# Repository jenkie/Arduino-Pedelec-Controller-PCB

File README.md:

# Arduino-Pedelec-Controller-PCB
PCB files for the Arduino Pedelec Controller

More info see http://www.pedelecforum.de/wiki/doku.php?id=elektrotechnik:forumscontroller

Shield: [![CC BY-NC 4.0][cc-by-nc-shield]][cc-by-nc]

This work is licensed under a
[Creative Commons Attribution-NonCommercial 4.0 International License][cc-by-nc].

[![CC BY-NC 4.0][cc-by-nc-image]][cc-by-nc]

[cc-by-nc]: https://creativecommons.org/licenses/by-nc/4.0/
[cc-by-nc-image]: https://licensebuttons.net/l/by-nc/4.0/88x31.png
[cc-by-nc-shield]: https://img.shields.io/badge/License-CC%20BY--NC%204.0-lightgrey.svg

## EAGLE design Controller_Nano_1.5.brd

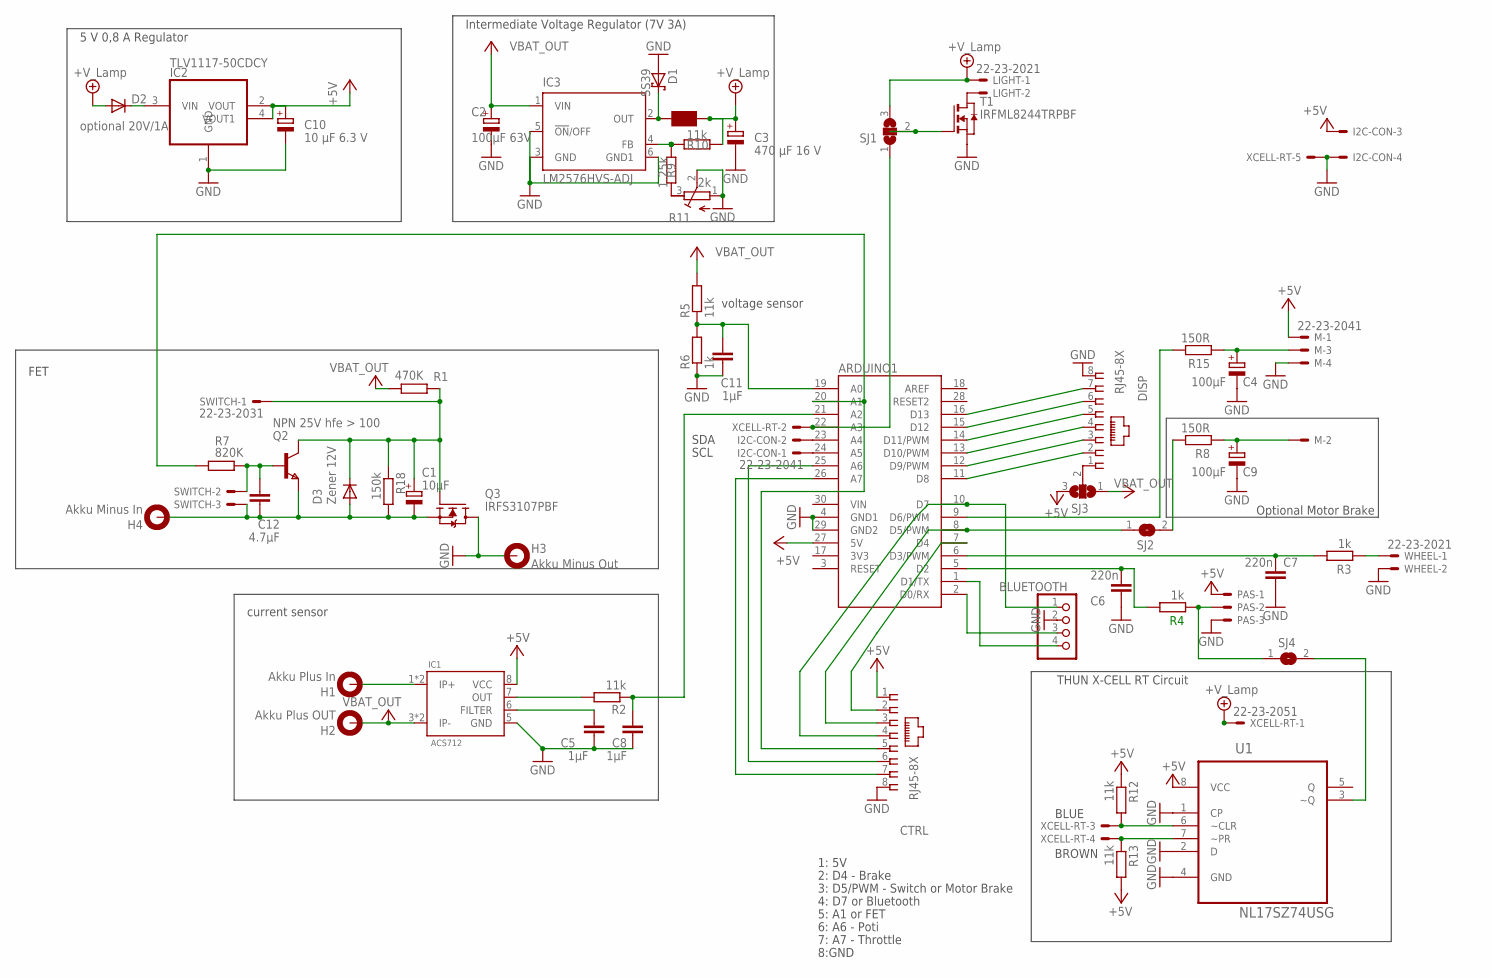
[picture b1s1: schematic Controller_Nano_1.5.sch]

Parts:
ARDUINO1: ARDUINO_NANO_CHECKED
BLUETOOTH: PINHD-1X4; 1X04
C1: 10µF; E2-5
C2: 100µF 63V; E3,5-8
C3: 470 µF 16 V; E3,5-8
C4, C9: 100µF; E2-5
C5, C8, C11: 1µF; C0805
C6, C7: 220n; C0805
C10: 10 µF 6.3 V; E2-5
C12: 4.7µF; C0805
CTRL: RJ45-8X; RJ45-NO-SHIELD
D1: SS39; SMC
D2: optional 20V/1A; DO-214AC
D3: Zener 12V; SOD323-W
DISP: RJ45-8X; RJ45-NO-SHIELD
H1: Akku Plus In; 2,8-PAD
H2: Akku Plus OUT; 2,8-PAD
H3: Akku Minus Out; 2,8-PAD
H4: Akku Minus In; 2,8-PAD
I2C-CON: 22-23-2041
IC1: ACS712; MARTIN-SMD-IC_SO-8
IC2: TLV1117-50CDCY; SOT223
IC3: LM2576HVS-ADJ; TO263-5
LIGHT: 22-23-2021; MPN 22-23-2021
M: 22-23-2041; MPN 22-23-2041
PAS: 22-23-2031
Q2: NPN 25V hfe > 100; SOT-23
Q3: IRFS3107PBF; TRANSISTOR-FET_TO263
R1: 470K; R1206
R2, R5, R10, R12, R13: 11k; R1206
R3, R4, R6: 1k; R1206
R7: 820K; R1206
R8, R15: 150R; R1206
R9: 1.25k; R1206
R11: 2k; RTRIM3103
R18: 150k; R1206
SJ1, SJ3: SJ2WW; SJ_2W
SJ2, SJ4: SJ
SWITCH: 22-23-2031; MPN 22-23-2031
T1: IRFML8244TRPBF; SOT-23
U1: NL17SZ74USG; SOP50P310X90-8N
U$1: PIST-151
WHEEL: 22-23-2021
XCELL-RT: 22-23-2051

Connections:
3V3: ARDUINO1.17 (3V3)
+5V: ARDUINO1.27 (5V), C10.+, CTRL.1, I2C-CON.3, IC1.8 (VCC), IC2.2 (VOUT), IC2.4 (VOUT1), M.1, PAS.1, R12.1, R13.2, SJ3.3, U1.8 (VCC)
+5V/2: C3.+, D2.A, LIGHT.1, R10.1, SJ1.3, U$1.P$2, XCELL-RT.1
GND: ARDUINO1.4 (GND1), ARDUINO1.29 (GND2), BLUETOOTH.2, C2.-, C3.-, C4.-, C5.2, C6.2, C7.2, C8.2, C9.-, C10.-, C11.2, CTRL.8, D1.A, DISP.8, H3.B2,8, I2C-CON.4, IC1.5 (GND), IC2.1 (GND), IC3.3 (GND), IC3.5 (!ON!/OFF), IC3.6 (GND1), M.4, PAS.3, Q3.2D (D), R6.1, R11.1 (E), R11.2 (S), T1.2 (S), U1.1 (CP), U1.2 (D), U1.4 (GND), WHEEL.2, XCELL-RT.5
unnamed: ARDUINO1.24 (A5), I2C-CON.1
unnamed: ARDUINO1.23 (A4), I2C-CON.2
unnamed: ARDUINO1.20 (A1), CTRL.5, R7.2
unnamed: ARDUINO1.16 (D13), DISP.7
unnamed: ARDUINO1.15 (D12), DISP.6
unnamed: ARDUINO1.14 (D11/PWM), DISP.5
unnamed: ARDUINO1.13 (D10/PWM), DISP.4
unnamed: ARDUINO1.12 (D9/PWM), DISP.3
unnamed: ARDUINO1.9 (D6/PWM), R15.2
unnamed: IC3.4 (FB), R9.2, R10.2
unnamed: LIGHT.2, T1.1 (D)
unnamed: C1.-, C12.2, D3.A, H4.B2,8, Q2.2 (E), Q3.3S (S), R18.2, SWITCH.3
unnamed: C1.+, D3.C, Q2.1 (C), Q3.1G (G), R1.2, R18.1, SWITCH.1
unnamed: R3.1, WHEEL.1
unnamed: D1.C, IC3.2 (OUT), U$1.P$1
unnamed: C5.1, IC1.6 (FILTER)
unnamed: ARDUINO1.19 (A0), C11.1, R5.1, R6.2
unnamed: ARDUINO1.22 (A3), SJ1.1, XCELL-RT.2
unnamed: ARDUINO1.7 (D4), CTRL.2
unnamed: ARDUINO1.8 (D5/PWM), CTRL.3, SJ2.1
unnamed: ARDUINO1.10 (D7), BLUETOOTH.1, CTRL.4
unnamed: C12.1, Q2.3 (B), R7.1, SWITCH.2
unnamed: ARDUINO1.11 (D8), DISP.2
unnamed: ARDUINO1.5 (D2), C6.1, R4.2
unnamed: IC1.7 (OUT), R2.2
unnamed: ARDUINO1.2 (D0/RX), BLUETOOTH.3
unnamed: ARDUINO1.25 (A6), CTRL.6
unnamed: ARDUINO1.26 (A7), CTRL.7
unnamed: ARDUINO1.1 (D1/TX), BLUETOOTH.4
unnamed: C9.+, M.2, R8.1
unnamed: C4.+, M.3, R15.1
unnamed: PAS.2, R4.1, SJ4.1
unnamed: ARDUINO1.6 (D3/PWM), C7.1, R3.2
unnamed: DISP.1, SJ3.2
unnamed: ARDUINO1.21 (A2), C8.1, R2.1
unnamed: SJ1.2, T1.3 (G)
unnamed: D2.C, IC2.3 (VIN)
unnamed: R8.2, SJ2.2
unnamed: R9.1, R11.3 (A)
unnamed: R12.2, U1.6 (~CLR), XCELL-RT.3
unnamed: R13.1, U1.7 (~PR), XCELL-RT.4
unnamed: SJ4.2, U1.3 (~Q)
VBAT_IN: H1.B2,8, IC1.1 (IP+), IC1.2 (IP+)
VBAT_OUT: C2.+, H2.B2,8, IC1.3 (IP-), IC1.4 (IP-), IC3.1 (VIN), R1.1, R5.2, SJ3.1

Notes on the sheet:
voltage sensor
current sensor
Intermediate Voltage Regulator (7V 3A)
1: 5V
2: D4 - Brake
3: D5/PWM - Switch or Motor Brake
4: D7 or Bluetooth
5: A1 or FET
6: A6 - Poti
7: A7 - Throttle
8:GND
SDA
SCL
FET
Optional Motor Brake
5 V 0,8 A Regulator
BLUE
BROWN
THUN X-CELL RT Circuit

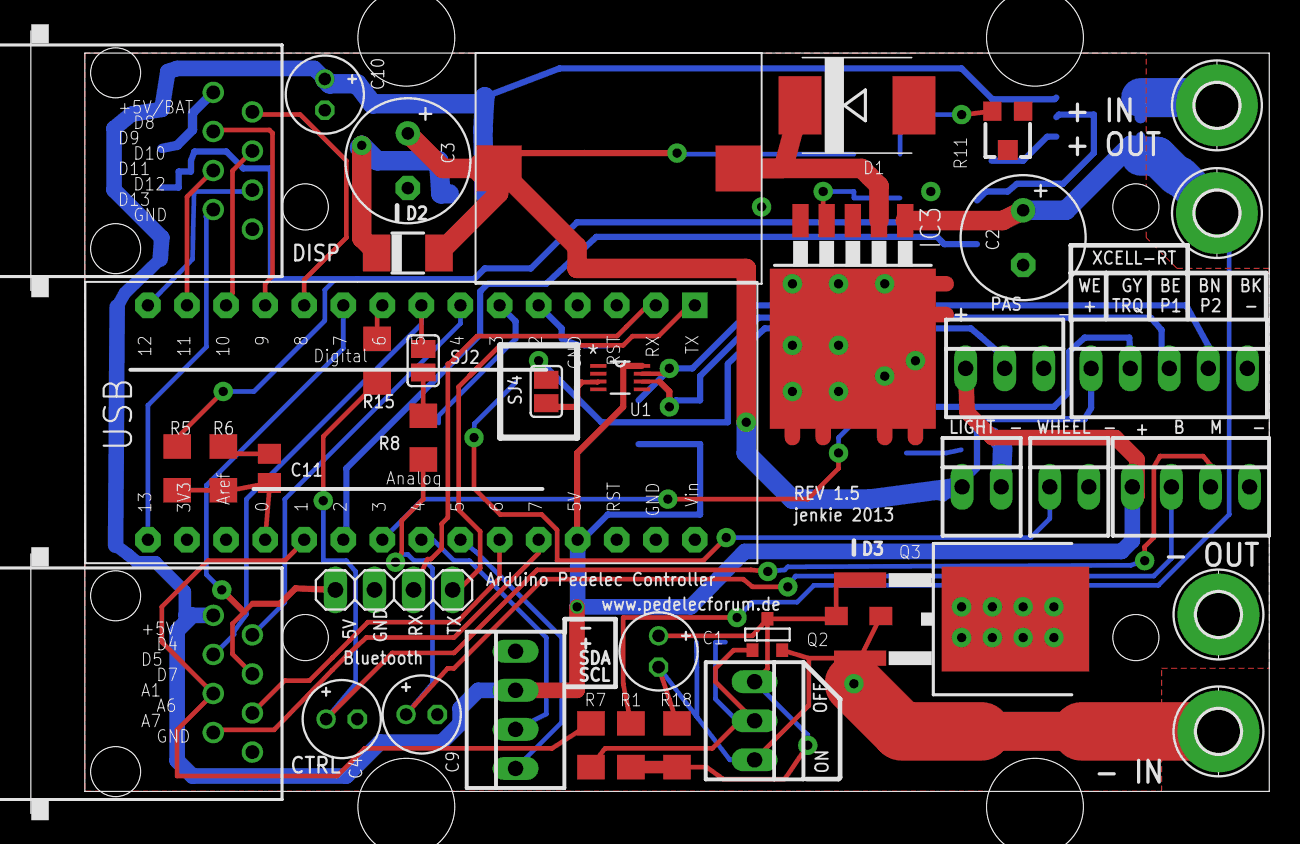
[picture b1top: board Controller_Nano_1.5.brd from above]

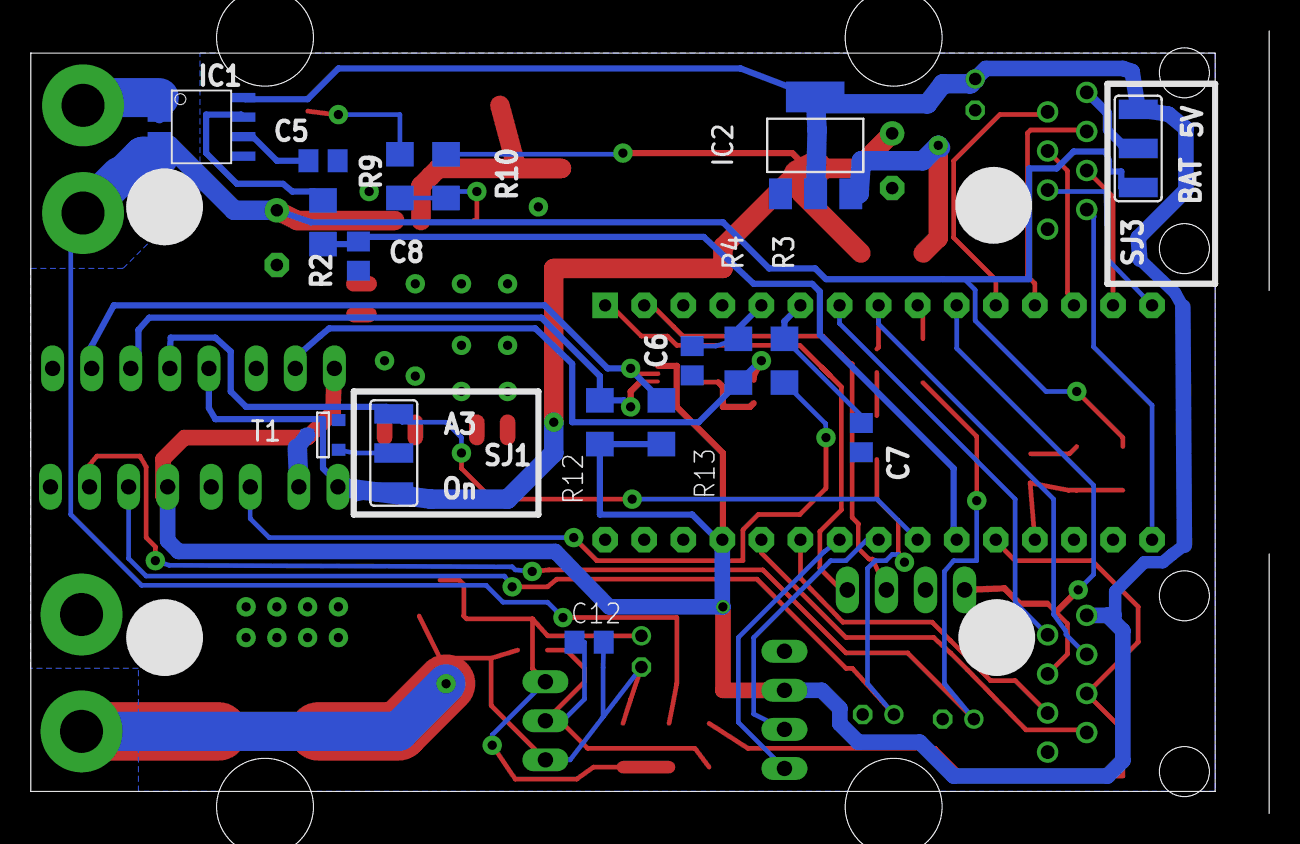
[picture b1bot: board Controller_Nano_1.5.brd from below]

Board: 2 copper layers, 80.5 x 50.9 mm, 58 parts (17 on the bottom side), 47 nets.

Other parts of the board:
U$2: 1593L

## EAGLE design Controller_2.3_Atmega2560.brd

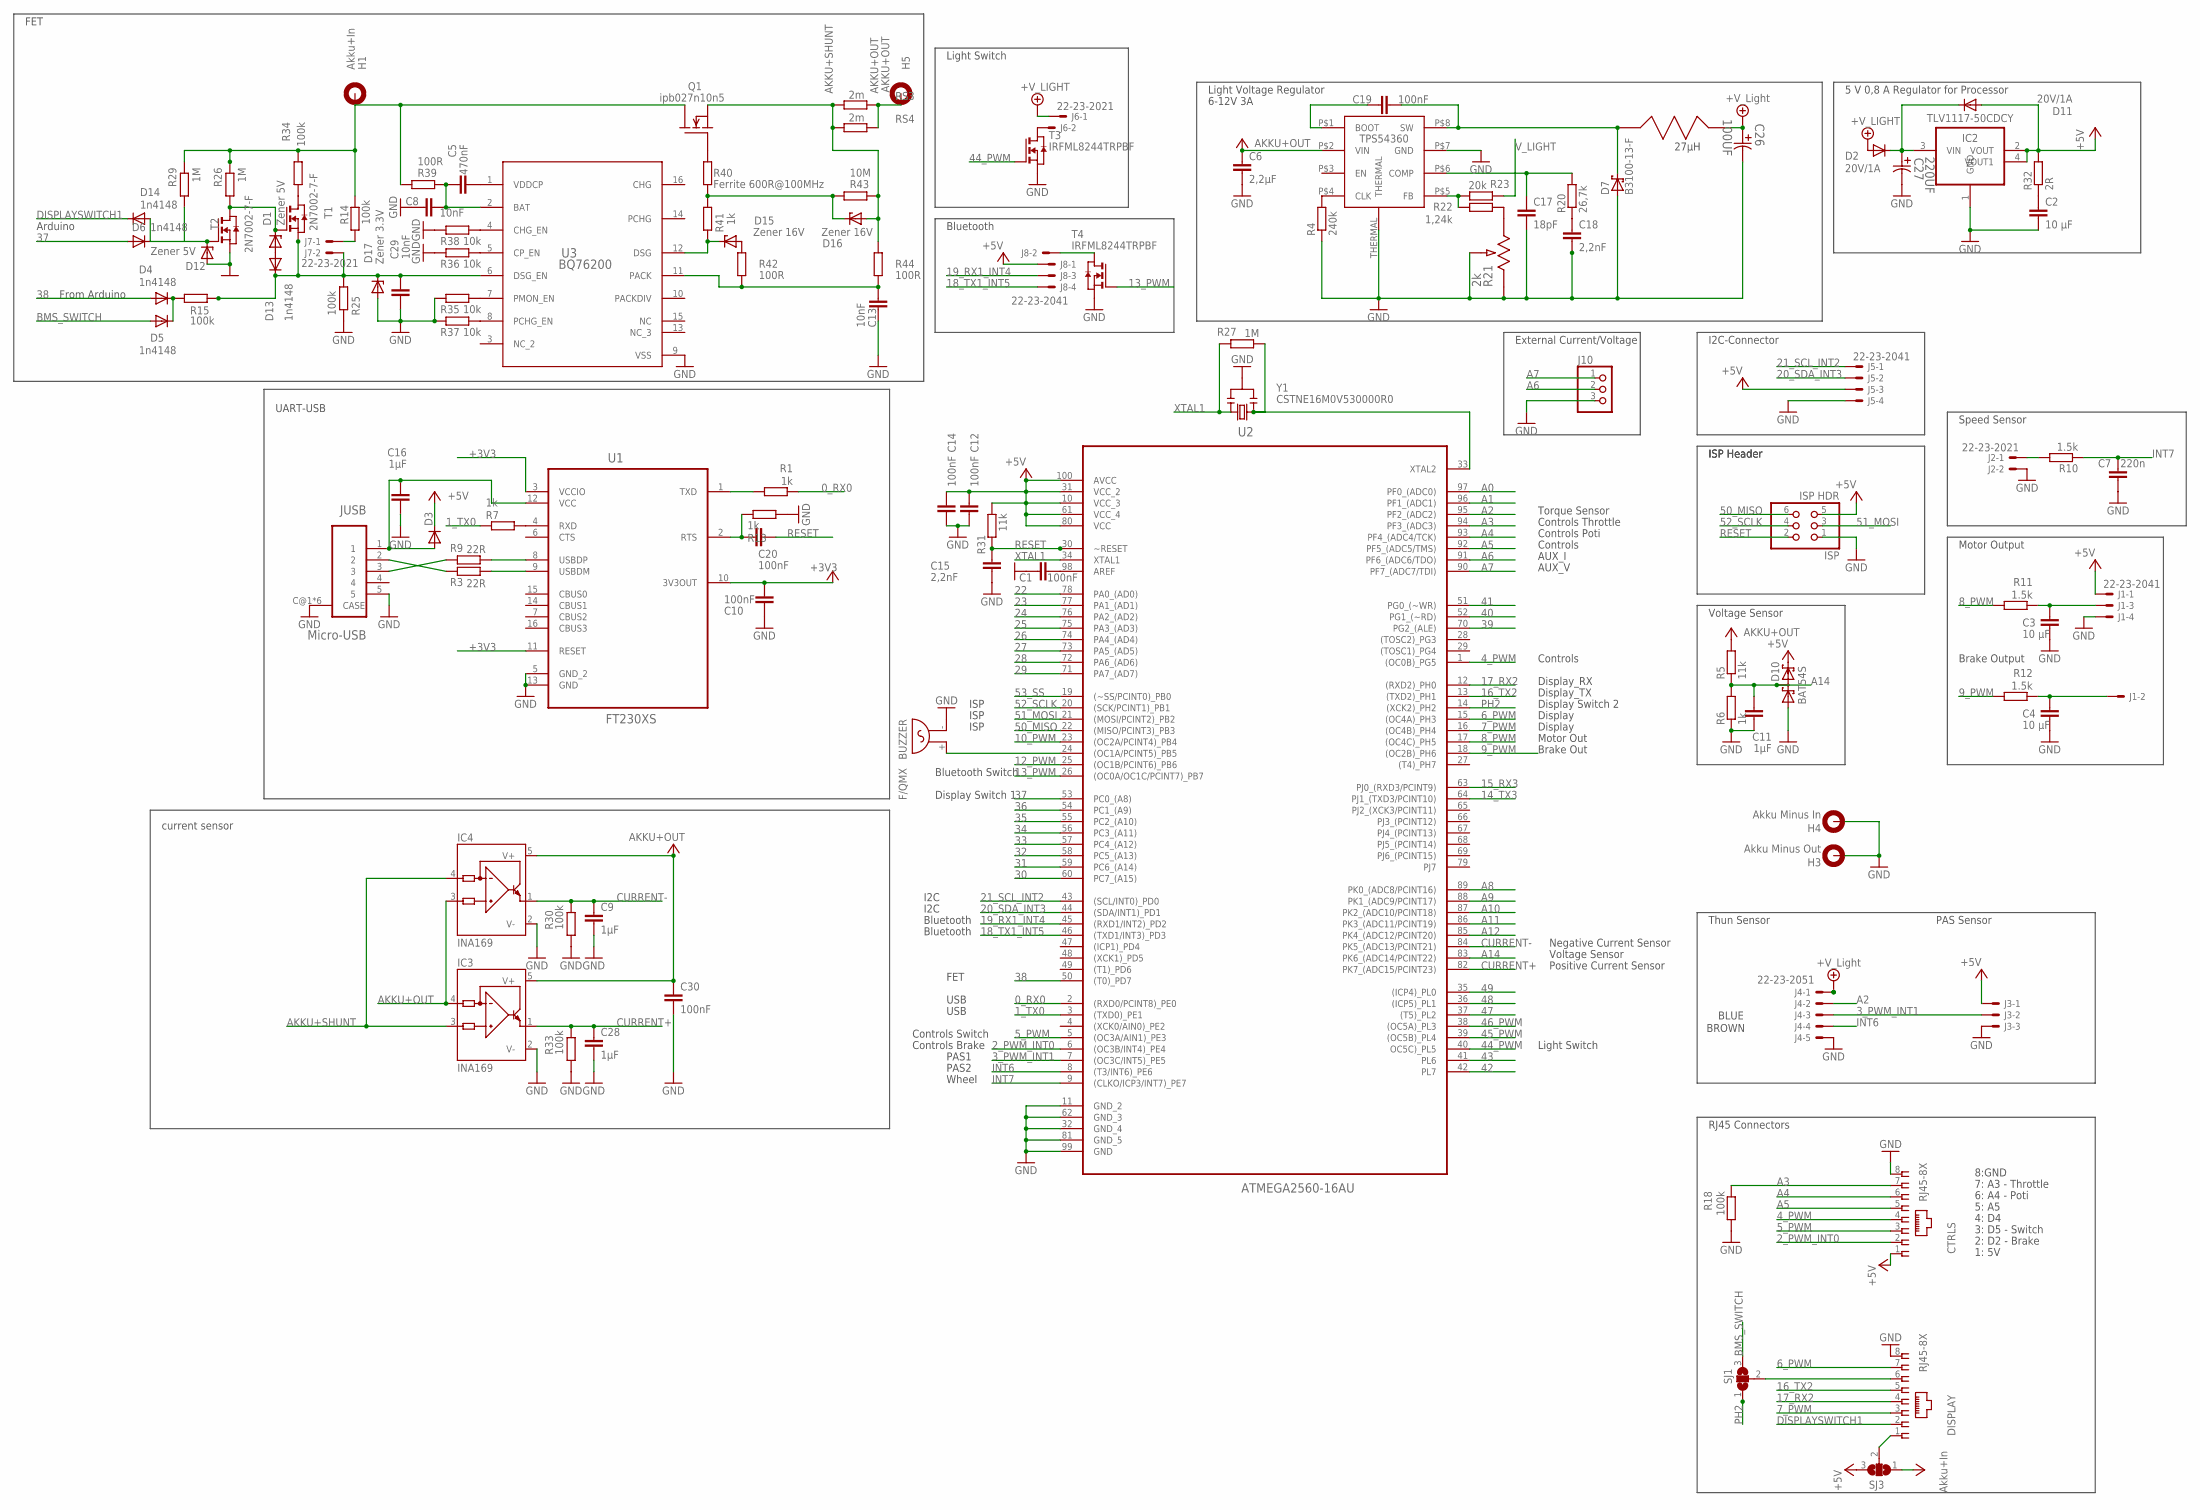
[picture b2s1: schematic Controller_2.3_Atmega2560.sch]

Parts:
BUZZER: F/QMX
C1, C10, C12, C14, C19, C20, C30: 100nF; C0603
C2, C3, C4: 10 µF; C1206
C5: 470nF; C0603
C6: 2,2µF; C1210
C7: 220n; C0603
C8, C13, C29: 10nF; C0603
C9, C11, C16, C28: 1µF; C0603
C15, C18: 2,2nF; C0603
C17: 18pF; C0603
C26: 100UF; CAPAE660X800N
C27: 220UF; CAPAE660X800N
CTRLS: RJ45-8X; RJ45-NO-SHIELD
D1, D12: Zener 5V; SOD323-W
D2, D3, D11: 20V/1A; DO-214AC
D4, D5, D6, D13, D14: 1n4148; SOD323-W
D7: B3100-13-F; SMC
D10: BAT54S; SOT23
D15, D16: Zener 16V; SOD323-W
D17: Zener 3.3V; SOD323-W
DISPLAY: RJ45-8X; RJ45-NO-SHIELD
H1: Akku+In; 2,8-PAD
H3: Akku Minus Out; 2,8-PAD
H4: Akku Minus In; 2,8-PAD
H5: AKKU+OUT; 2,8-PAD
IC2: TLV1117-50CDCY; SOT223
IC3, IC4: INA169; SOT23-5
ISP: ISP HDR; 2X03
J1: 22-23-2041; MPN 22-23-2041
J2, J7: 22-23-2021
J3: 22-23-2031
J4: 22-23-2051
J5, J8: 22-23-2041
J6: 22-23-2021; MPN 22-23-2021
J10: PINHD-1X3; 1X03
JUSB: Micro-USB; MOLEX_47346-0001
Q1: ipb027n10n5; D2PAK
R1, R6, R7, R13, R41: 1k; R0603
R3, R9: 22R; R0603
R4: 240k; R0603
R5, R31: 11k; R0603
R10, R11, R12: 1.5k; R0603
R14, R15, R18, R25, R30, R33, R34: 100k; R0603
R20: 26,7k; R0603
R21: 2k; POT_EVM3W
R22: 1,24k; R0603
R23: 20k; R0603
R26, R27, R29: 1M; R0603
R32: 2R; R0603
R35, R36, R37, R38: 10k; R0603
R39, R42, R44: 100R; R0603
R40: Ferrite 600R@100MHz; R0603
R43: 10M; R0603
RS3, RS4: 2m; R2512
SJ1, SJ3: SJ2W; SJ_2
T1, T2: 2N7002-7-F; SOT-23
T3, T4: IRFML8244TRPBF; SOT-23
U1: FT230XS; SOP63P600X175-16N
U2: ATMEGA2560-16AU; QFP50P1600X1600X120-100N
U3: BQ76200; PW0016A_N
U9: SRR1260-270M; ARR1260
U11: TPS54360; R-PDSO-G8
Y1: CSTNE16M0V530000R0; RESONATOR

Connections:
0_RX0: R1.1, U2.2 ((RXD0/PCINT8)_PE0)
1_TX0: R7.1, U2.3 ((TXD0)_PE1)
2_PWM_INT0: CTRLS.2, U2.6 ((OC3B/INT4)_PE4)
3_PWM_INT1: J3.2, J4.3, U2.7 ((OC3C/INT5)_PE5)
4_PWM: CTRLS.4, U2.1 ((OC0B)_PG5)
5_PWM: CTRLS.3, U2.5 ((OC3A/AIN1)_PE3)
6_PWM: DISPLAY.7, U2.15 ((OC4A)_PH3)
7_PWM: DISPLAY.3, U2.16 ((OC4B)_PH4)
8_PWM: R11.2, U2.17 ((OC4C)_PH5)
9_PWM: R12.2, U2.18 ((OC2B)_PH6)
10_PWM: U2.23 ((OC2A/PCINT4)_PB4)
12_PWM: U2.25 ((OC1B/PCINT6)_PB6)
13_PWM: T4.3 (G), U2.26 ((OC0A/OC1C/PCINT7)_PB7)
14_TX3: U2.64 (PJ1_(TXD3/PCINT10))
15_RX3: U2.63 (PJ0_(RXD3/PCINT9))
16_TX2: DISPLAY.5, U2.13 ((TXD2)_PH1)
17_RX2: DISPLAY.4, U2.12 ((RXD2)_PH0)
18_TX1_INT5: J8.4, U2.46 ((TXD1/INT3)_PD3)
19_RX1_INT4: J8.3, U2.45 ((RXD1/INT2)_PD2)
20_SDA_INT3: J5.2, U2.44 ((SDA/INT1)_PD1)
21_SCL_INT2: J5.1, U2.43 ((SCL/INT0)_PD0)
22: U2.78 (PA0_(AD0))
23: U2.77 (PA1_(AD1))
24: U2.76 (PA2_(AD2))
25: U2.75 (PA3_(AD3))
26: U2.74 (PA4_(AD4))
27: U2.73 (PA5_(AD5))
28: U2.72 (PA6_(AD6))
29: U2.71 (PA7_(AD7))
30: U2.60 (PC7_(A15))
31: U2.59 (PC6_(A14))
32: U2.58 (PC5_(A13))
33: U2.57 (PC4_(A12))
34: U2.56 (PC3_(A11))
35: U2.55 (PC2_(A10))
36: U2.54 (PC1_(A9))
37: D6.A, U2.53 (PC0_(A8))
38: D4.A, U2.50 ((T0)_PD7)
39: U2.70 (PG2_(ALE))
40: U2.52 (PG1_(~RD))
41: U2.51 (PG0_(~WR))
42: U2.42 (PL7)
43: U2.41 (PL6)
44_PWM: T3.3 (G), U2.40 (OC5C)_PL5)
45_PWM: U2.39 ((OC5B)_PL4)
46_PWM: U2.38 ((OC5A)_PL3)
47: U2.37 ((T5)_PL2)
48: U2.36 ((ICP5)_PL1)
49: U2.35 ((ICP4)_PL0)
50_MISO: ISP.6, U2.22 ((MISO/PCINT3)_PB3)
51_MOSI: ISP.3, U2.21 ((MOSI/PCINT2)_PB2)
52_SCLK: ISP.4, U2.20 ((SCK/PCINT1)_PB1)
53_SS: U2.19 ((~SS/PCINT0)_PB0)
+3V3: C10.2, U1.3 (VCCIO), U1.10 (3V3OUT), U1.11 (RESET)
+5V: C12.2, C14.2, CTRLS.1, D3.C, D10.2 (C2), D11.A, IC2.2 (VOUT), IC2.4 (VOUT1), ISP.5, J1.1, J3.1, J5.3, J8.1, R31.2, R32.2, SJ3.3, U2.10 (VCC_3), U2.31 (VCC_2), U2.61 (VCC_4), U2.80 (VCC), U2.100 (AVCC)
A0: U2.97 (PF0_(ADC0))
A1: U2.96 (PF1_(ADC1))
A2: J4.2, U2.95 (PF2_(ADC2))
A3: CTRLS.7, R18.1, U2.94 (PF3_(ADC3))
A4: CTRLS.6, U2.93 (PF4_(ADC4/TCK))
A5: CTRLS.5, U2.92 (PF5_(ADC5/TMS))
A6: J10.2, U2.91 (PF6_(ADC6/TDO))
A7: J10.1, U2.90 (PF7_(ADC7/TDI))
A8: U2.89 (PK0_(ADC8/PCINT16))
A9: U2.88 (PK1_(ADC9/PCINT17))
A10: U2.87 (PK2_(ADC10/PCINT18))
A11: U2.86 (PK3_(ADC11/PCINT19))
A12: U2.85 (PK4_(ADC12/PCINT20))
A14: C11.1, D10.3 (C1A2), R5.1, R6.2, U2.83 (PK6_(ADC14/PCINT22))
AKKU+IN: H1.B2,8, Q1.2 (D), R14.2, R26.1, R29.1, R34.1, R39.2, SJ3.1
AKKU+OUT: C6.1, C30.1, H5.B2,8, IC3.4 (IN-), IC3.5 (V+), IC4.3 (IN+), IC4.5 (V+), R5.2, RS3.2, RS4.2, U11.P$2 (VIN)
AKKU+SHUNT: D16.A, IC3.3 (IN+), IC4.4 (IN-), Q1.3 (S), R43.1, R44.2, RS3.1, RS4.1
BMS_SWITCH: D5.A, SJ1.3
CURRENT+: C28.1, IC3.1 (OUT), R33.2, U2.82 (PK7_(ADC15/PCINT23))
CURRENT-: C9.1, IC4.1 (OUT), R30.2, U2.84 (PK5_(ADC13/PCINT21))
DISPLAYSWITCH1: D14.C, DISPLAY.2
GND: BUZZER.- (1), C1.2, C2.2, C3.2, C4.2, C6.2, C7.2, C8.1, C9.2, C10.1, C11.2, C12.1, C13.1, C14.1, C15.2, C16.2, C17.2, C18.2, C26.2, C27.2, C28.2, C29.1, C30.2, CTRLS.8, D7.A, D10.1 (A1), D12.A, D17.A, DISPLAY.8, H3.B2,8, H4.B2,8, IC2.1 (GND), IC3.2 (V-), IC4.2 (V-), ISP.1, J1.4, J2.2, J3.3, J4.5, J5.4, J10.3, JUSB.5, JUSB.C@1 (CASE), JUSB.C@2 (CASE), JUSB.C@3 (CASE), JUSB.C@4 (CASE), JUSB.C@5 (CASE), JUSB.C@6 (CASE), R4.1, R6.1, R13.2, R18.2, R21.1, R21.2, R25.1, R30.1, R33.1, R35.2, R36.2, R37.2, R38.2, T2.2 (S), T3.2 (S), T4.2 (S), U1.5 (GND_2), U1.13 (GND), U2.11 (GND_2), U2.32 (GND_4), U2.62 (GND_3), U2.81 (GND_5), U2.99 (GND), U3.9 (VSS), U11.P$7 (GND), U11.THERMAL, Y1.2
INT6: J4.4, U2.8 ((T3/INT6)_PE6)
INT7: C7.1, R10.1, U2.9 ((CLKO/ICP3/INT7)_PE7)
unnamed: J6.2, T3.1 (D)
unnamed: R4.2, U11.P$4 (CLK)
unnamed: C16.1, D3.A, JUSB.1, U1.12 (VCC)
unnamed: C1.1, U2.98 (AREF)
unnamed: J8.2, T4.1 (D)
unnamed: C20.1, R13.1, U1.2 (RTS)
unnamed: R3.1, U1.9 (USBDM)
unnamed: R9.1, U1.8 (USBDP)
unnamed: R1.2, U1.1 (TXD)
unnamed: JUSB.2, R3.2
unnamed: C2.1, R32.1
unnamed: R7.2, U1.4 (RXD)
unnamed: R21.3, R22.1
unnamed: J2.1, R10.2
unnamed: JUSB.3, R9.2
unnamed: D1.A, D13.A
unnamed: C18.1, R20.1
unnamed: C17.1, R20.2, U11.P$6 (COMP)
unnamed: BUZZER.+ (2), U2.24 ((OC1A/PCINT5)_PB5)
unnamed: R34.2, T1.1 (D)
unnamed: R37.1, U3.8 (PCHG_EN)
unnamed: R22.2, R23.2, U11.P$5 (FB)
unnamed: D4.C, D5.C, R15.1
unnamed: R35.1, U3.7 (PMON_EN)
unnamed: C3.1, J1.3, R11.1
unnamed: C4.1, J1.2, R12.1
unnamed: C19.2, D7.C, U9.P$1, U11.P$8 (SW)
unnamed: DISPLAY.1, SJ3.2
unnamed: J7.1, R14.1
unnamed: C27.1, D2.C, D11.C, IC2.3 (VIN)
unnamed: R36.1, U3.5 (CP_EN)
unnamed: R38.1, U3.4 (CHG_EN)
unnamed: C5.2, U3.1 (VDDCP)
unnamed: D1.C, R26.2, T1.3 (G), T2.1 (D)
unnamed: C19.1, U11.P$1 (BOOT)
unnamed: C5.1, C8.2, R39.1, U3.2 (BAT)
unnamed: C29.2, D13.C, D17.C, J7.2, R15.2, R25.2, T1.2 (S), U3.6 (DSG_EN)
unnamed: DISPLAY.6, SJ1.2
unnamed: D15.A, R42.2
unnamed: D6.C, D12.C, D14.A, R29.2, T2.3 (G)
unnamed: C13.2, R42.1, R44.1, U3.11 (PACK)
unnamed: Q1.1 (G), R40.2
unnamed: D16.C, R40.1, R41.2, R43.2
unnamed: D15.C, R41.1, U3.12 (DSG)
unnamed: R27.1, U2.33 (XTAL2), Y1.1
PH2: SJ1.1, U2.14 ((XCK2)_PH2)
RESET: C15.1, C20.2, ISP.2, R31.1, U2.30 (~RESET)
V_LIGHT: C26.1, D2.A, J4.1, J6.1, R23.1, U9.P$2
XTAL1: R27.2, U2.34 (XTAL1), Y1.3

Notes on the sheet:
Voltage Sensor
current sensor
1: 5V
2: D2 - Brake
3: D5 - Switch
4: D4
5: A5
6: A4 - Poti
7: A3 - Throttle
8:GND
FET
5 V 0,8 A Regulator for Processor
BLUE
BROWN
ISP Header
I2C-Connector
Thun Sensor
PAS Sensor
Speed Sensor
Light Voltage Regulator
6-12V 3A
Motor Output
Brake Output
Light Switch
RJ45 Connectors
27µH
UART-USB
PAS1
PAS2
Bluetooth
USB
Bluetooth Switch
Positive Current Sensor
Torque Sensor
Wheel
Motor Out
Brake Out
Display_RX
Display_TX
Display Switch 2

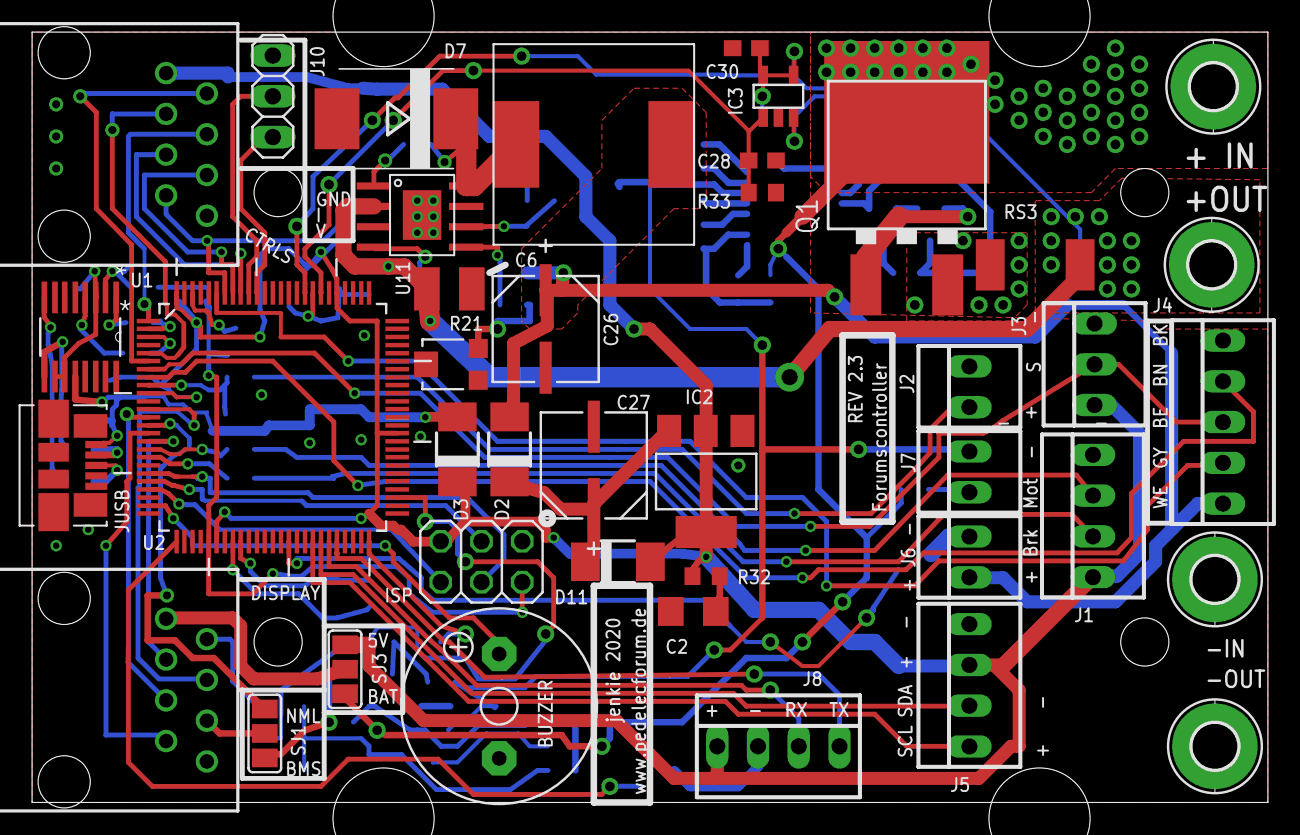
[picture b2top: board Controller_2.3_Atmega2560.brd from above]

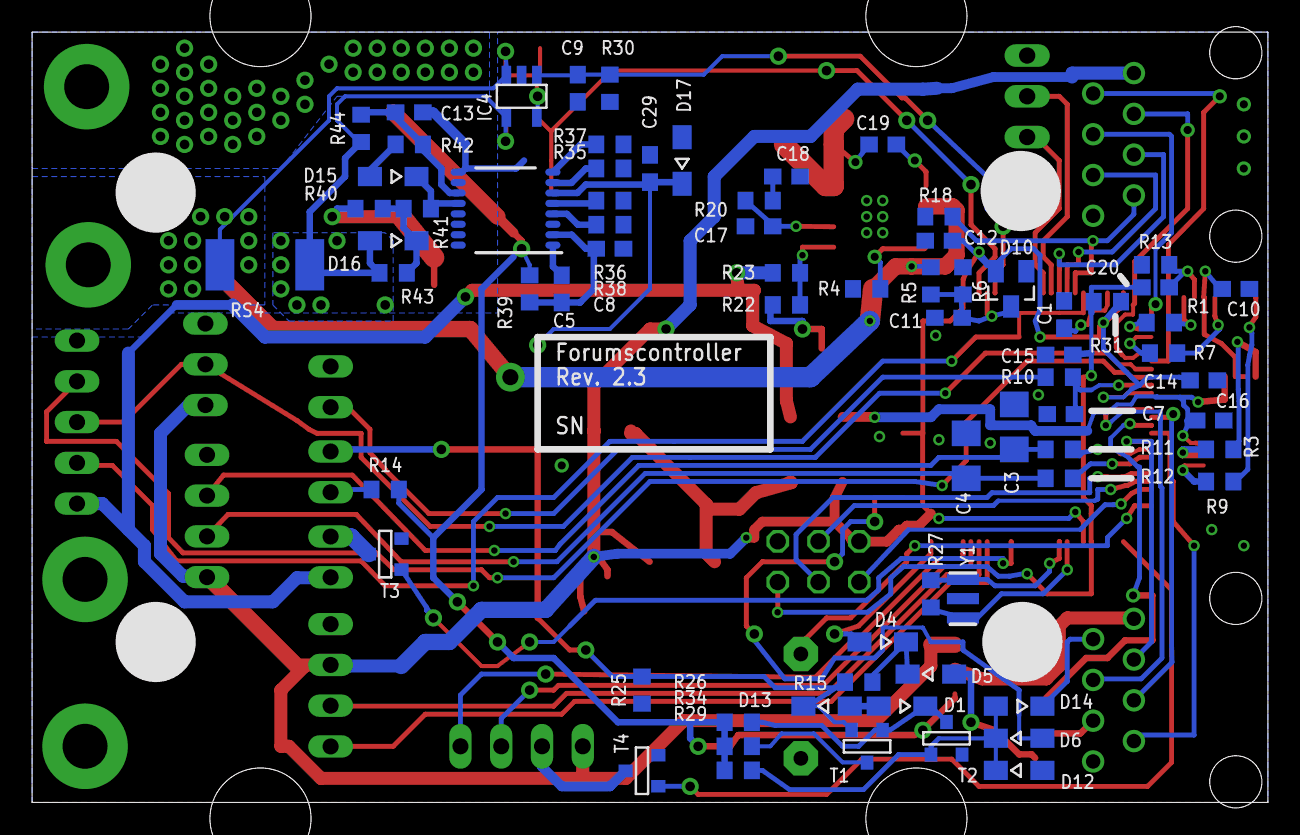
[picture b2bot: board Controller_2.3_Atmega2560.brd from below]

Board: 2 copper layers, 77.0 x 48.0 mm, 114 parts (72 on the bottom side), 91 nets.

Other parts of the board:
U$2: 1593L
